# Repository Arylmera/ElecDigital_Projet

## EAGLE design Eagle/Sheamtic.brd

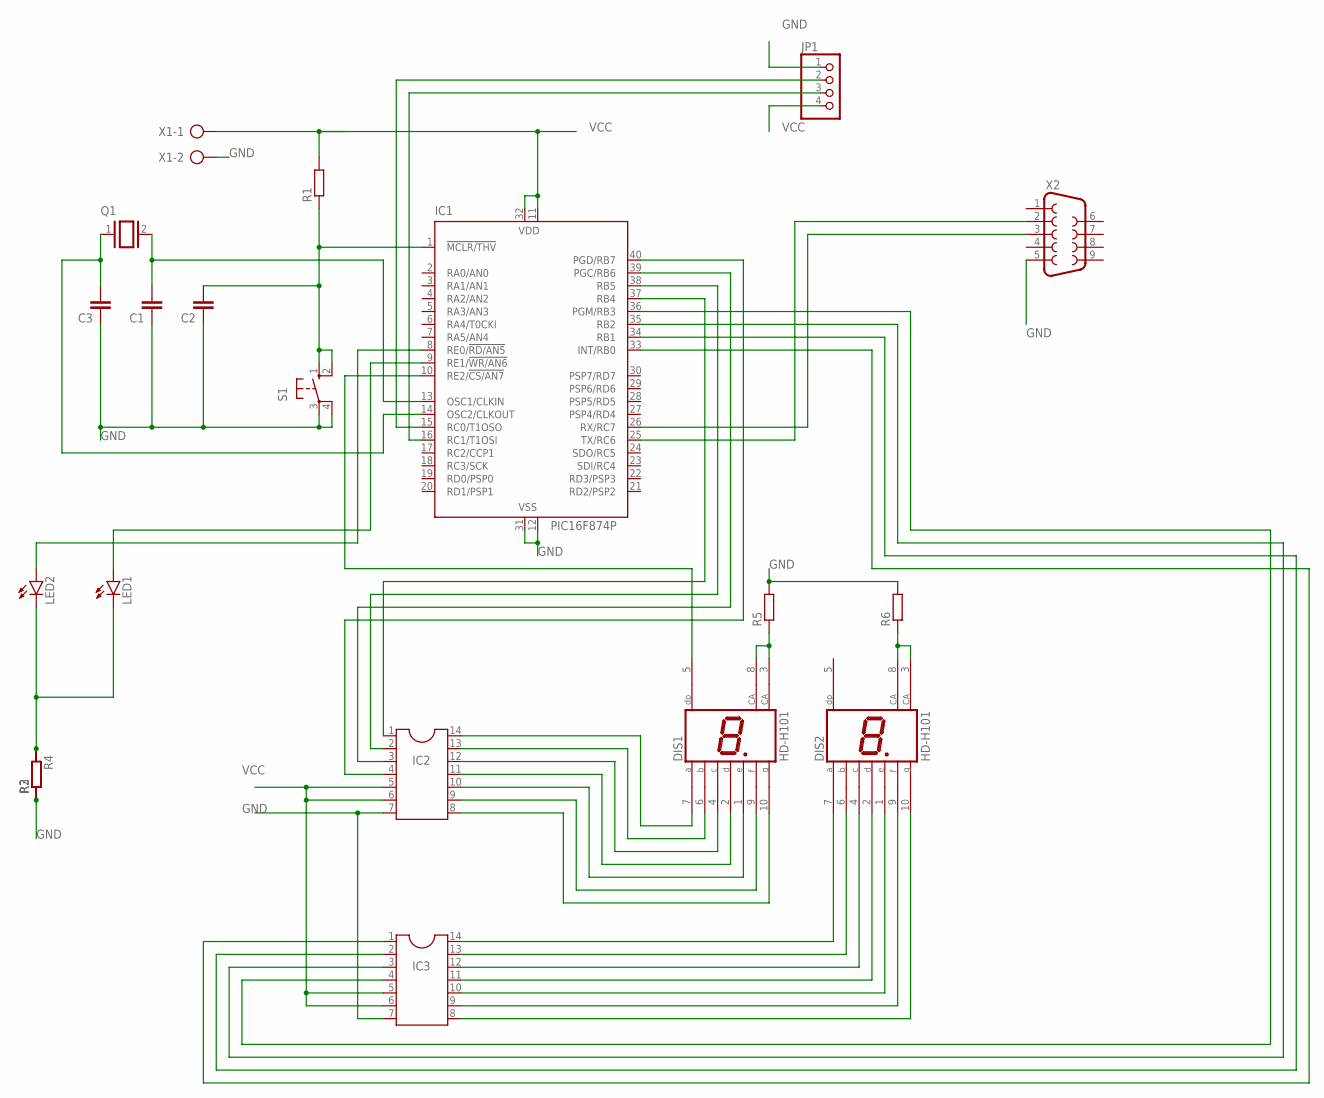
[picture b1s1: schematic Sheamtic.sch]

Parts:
C1, C2, C3: C-EU025-025X050; C025-025X050
DIS1, DIS2: HD-H101; HDSP-M
IC1: PIC16F874P; DIL40
IC2, IC3: DIL14
JP1: PINHD-1X4; 1X04
LED1, LED2: LED5MM
Q1: XTAL/S; QS
R1, R2, R3, R4, R5, R6: R-EU_0204/7; 0204/7
S1: 10-XX; B3F-10XX
X1: AK300/2
X2: F09HP

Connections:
GND: C1.1, C2.1, C3.1, DIS1.3 (CA), DIS1.8 (CA), IC1.12 (VSS), IC1.31 (VSS), IC2.7, IC3.7, JP1.1, R2.1, R3.1, R4.2, R5.1, R5.2, R6.2, S1.3, S1.4 (P1), X1.2, X2.5
unnamed: DIS1.7 (A), IC2.14
unnamed: C2.2, IC1.1 (!MCLR/THV), R1.1, S1.1 (S), S1.2 (S1)
unnamed: IC1.15 (RC0/T1OSO), JP1.2
unnamed: IC1.37 (RB4), IC2.1
unnamed: C3.2, IC1.14 (OSC2/CLKOUT), Q1.1
unnamed: IC1.25 (TX/RC6), X2.2
unnamed: IC1.26 (RX/RC7), X2.3
unnamed: IC1.38 (RB5), IC2.2
unnamed: C1.2, IC1.13 (OSC1/CLKIN), Q1.2
unnamed: IC1.39 (PGC/RB6), IC2.3
unnamed: IC1.33 (INT/RB0), IC3.1
unnamed: IC1.34 (RB1), IC3.2
unnamed: IC1.35 (RB2), IC3.3
unnamed: IC1.36 (PGM/RB3), IC3.4
unnamed: IC1.8 (RE0/!RD/AN5), LED2.A
unnamed: IC1.9 (RE1/!WR/AN6), LED1.A
unnamed: LED1.K (C), LED2.K (C), R2.2, R3.2, R4.1
unnamed: DIS1.6 (B), IC2.13
unnamed: DIS1.4 (C), IC2.12
unnamed: DIS1.2 (D), IC2.11
unnamed: DIS1.1 (E), IC2.10
unnamed: DIS1.9 (F), IC2.9
unnamed: DIS1.10 (G), IC2.8
unnamed: DIS2.7 (A), IC3.14
unnamed: DIS2.6 (B), IC3.13
unnamed: DIS2.4 (C), IC3.12
unnamed: DIS2.2 (D), IC3.11
unnamed: DIS2.1 (E), IC3.10
unnamed: DIS2.9 (F), IC3.9
unnamed: DIS2.10 (G), IC3.8
unnamed: IC1.16 (RC1/T1OSI), JP1.3
unnamed: IC1.40 (PGD/RB7), IC2.4
unnamed: DIS1.5 (DP), IC1.10 (RE2/!CS/AN7)
unnamed: DIS2.3 (CA), DIS2.8 (CA), R6.1
VCC: IC1.11 (VDD), IC1.32 (VDD), IC2.5, IC2.6, IC3.5, IC3.6, JP1.4, R1.2, X1.1

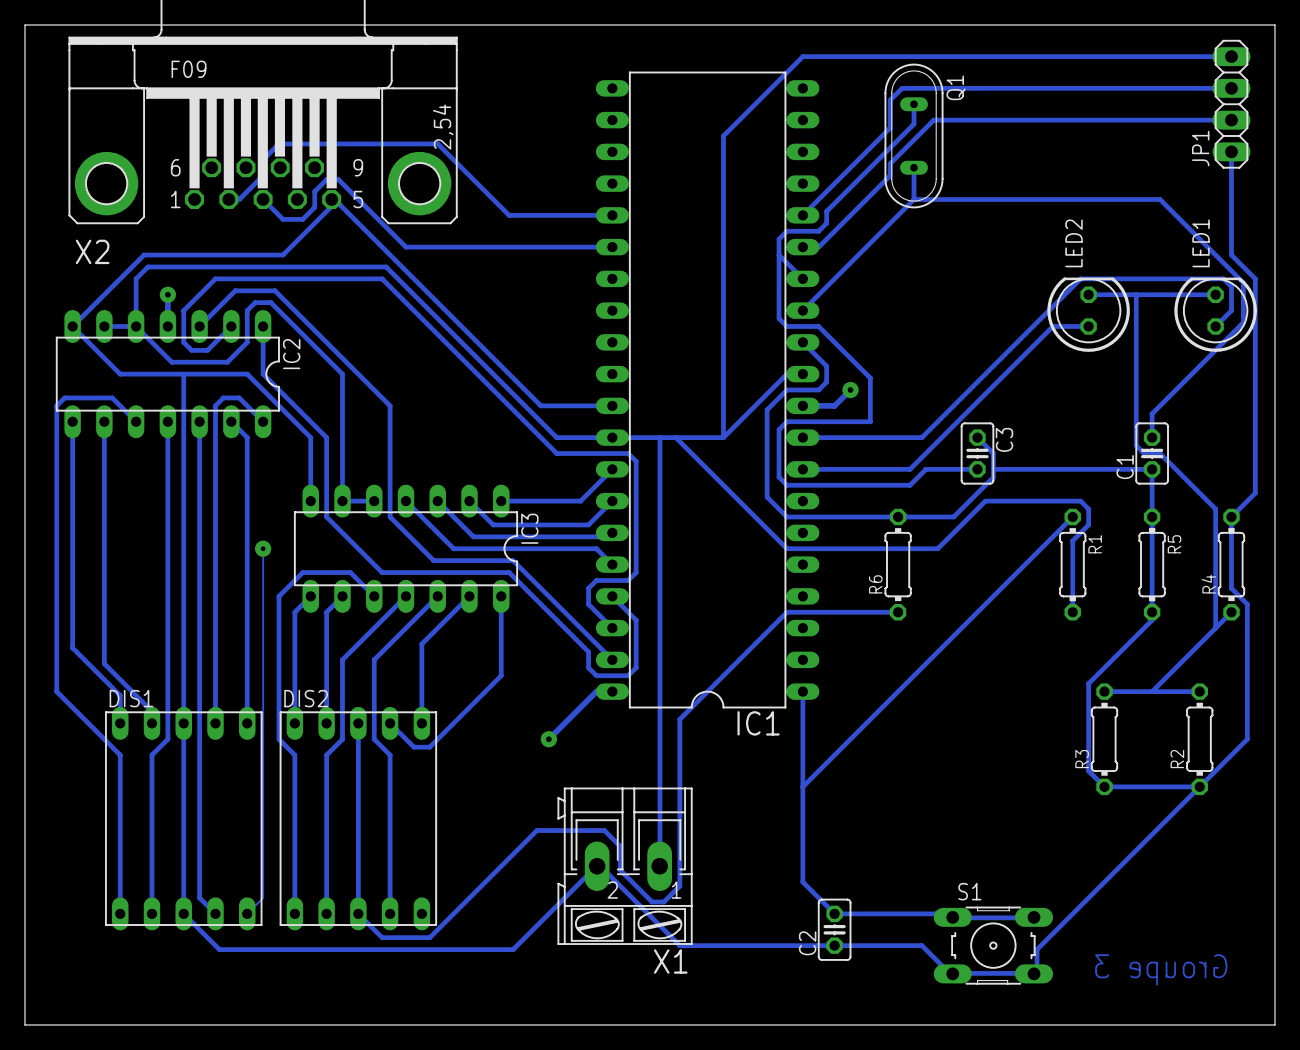
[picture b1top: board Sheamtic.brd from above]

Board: 2 copper layers, 100.0 x 80.0 mm, 21 parts (0 on the bottom side), 36 nets.

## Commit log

2020-02-13 add dossier proteus
2020-02-17 add ficheir eagle en construction"
    "
2020-02-17 eagle v2
2020-02-17 proteus
2020-02-19 eagle add res
2020-02-20 proteus port CONPIM && CC
2020-02-22 Add files via upload
    Cablage, voir afficheur 7 seg car pas logique nombre entrée/sortie diff par rapport à proteus
2020-02-24 Eagle
2020-02-27 correction proteus/eagle + test pic ccs
2020-03-02 proteus et ccs
2020-03-02 ccs et proteus v2
2020-03-02 eagle update
2020-03-03 board
2020-03-03 add print proteus
2020-03-03 add print screen eagle
2020-03-03 fonction parsing output
2020-03-04 update board
2020-03-06 clean
2020-03-07 ccs
    manque implémentation timer
2020-03-07 ccs
    valeur bonne manque parsing
2020-03-09 add rapport
2020-03-12 Texte couche 16
2020-03-19 Create Commu Serial
2020-03-19 Ajout interface basique java
2020-03-20 ajout condition pour textfield
2020-03-21 add button action
2020-03-21 add getter setter
2020-03-27 fix inteliji
2020-03-30 timer suite
2020-04-03 Code C
2020-04-11 correction code ccs
    Correction code ccs
2020-04-11 CCS fix int16
2020-04-11 time -> dist v1
2020-04-13 code C fix and clean
2020-04-19 add jar
2020-04-19 1er fix code java
2020-04-19 java
2020-04-19 clean code and dependancies
2020-04-19 java code
2020-04-19 comments java
2020-04-19 séparation codes java
2020-04-21 java log
2020-04-21 manifest
2020-04-22 Java interface
2020-04-22 add RxTx
2020-04-22 Update Elec
2020-04-23 version RxTx
2020-04-23 fix push
2020-04-23 fix size
2020-04-23 RxTx fix
2020-04-23 Maj code et RxTx
2020-04-23 test
2020-04-24 add close and try catch error
2020-04-24 fix close
2020-04-24 add exit
2020-04-24 print max value
2020-04-24 data read
2020-04-27 comment LCD
2020-04-27 fix include
2020-04-27 Fix main.c
2020-04-27 compile main.c
2020-04-27 maj LCD
2020-04-27 comments
2020-05-03 fix bauds
2020-05-03 python v1
2020-05-03 python read OK
2020-05-03 python GUI
2020-05-03 add color
2020-05-03 Gui Layout
2020-05-03 commentaire Python
2020-05-03 default value entry python gui
2020-05-03 Fix c
2020-05-03 Working on main.c
2020-05-03 Still not working
2020-05-06 Fix All
2020-05-06 fix chiffres < 100
2020-05-09 rapport
2020-05-13 last push
